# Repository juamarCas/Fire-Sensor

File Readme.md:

# Fire sensor network
This project conssists on a prototype of a Wireless Sensor Network(WSN) for fire detection.
The design is made in Ki-Cad
## Sensor node
It uses the Atmega328 (Arduino one).
connector J1 you can connect a battery to measure the energy left.

### Code
the code for each sensor is in  _Transmmiter.ino_ 
when you configure the channels you have to know that it has to be a
number in octal format like this:
```
int this_node = 01; 
```

## Base node
It uses NodeMCU with the ESP8266, 

### Code 
the code is _BaseNode2.ino_
also use octal form for channels

## Libraries
-We used the nrf24L01 library to communicate each node, you can find the library here [GitHub Pages](https://github.com/nRF24/RF24)

-To make a network we used nrf24l01 network library [GitHub Pages](https://github.com/nRF24/RF24Network)

-To meassure temperature and humidity we used the DTH22 library 
[GitHub Pages](https://github.com/adafruit/DHT-sensor-library)

-To send data to the server we used ArduinoJson [ArduinoJson] (https://arduinojson.org/)

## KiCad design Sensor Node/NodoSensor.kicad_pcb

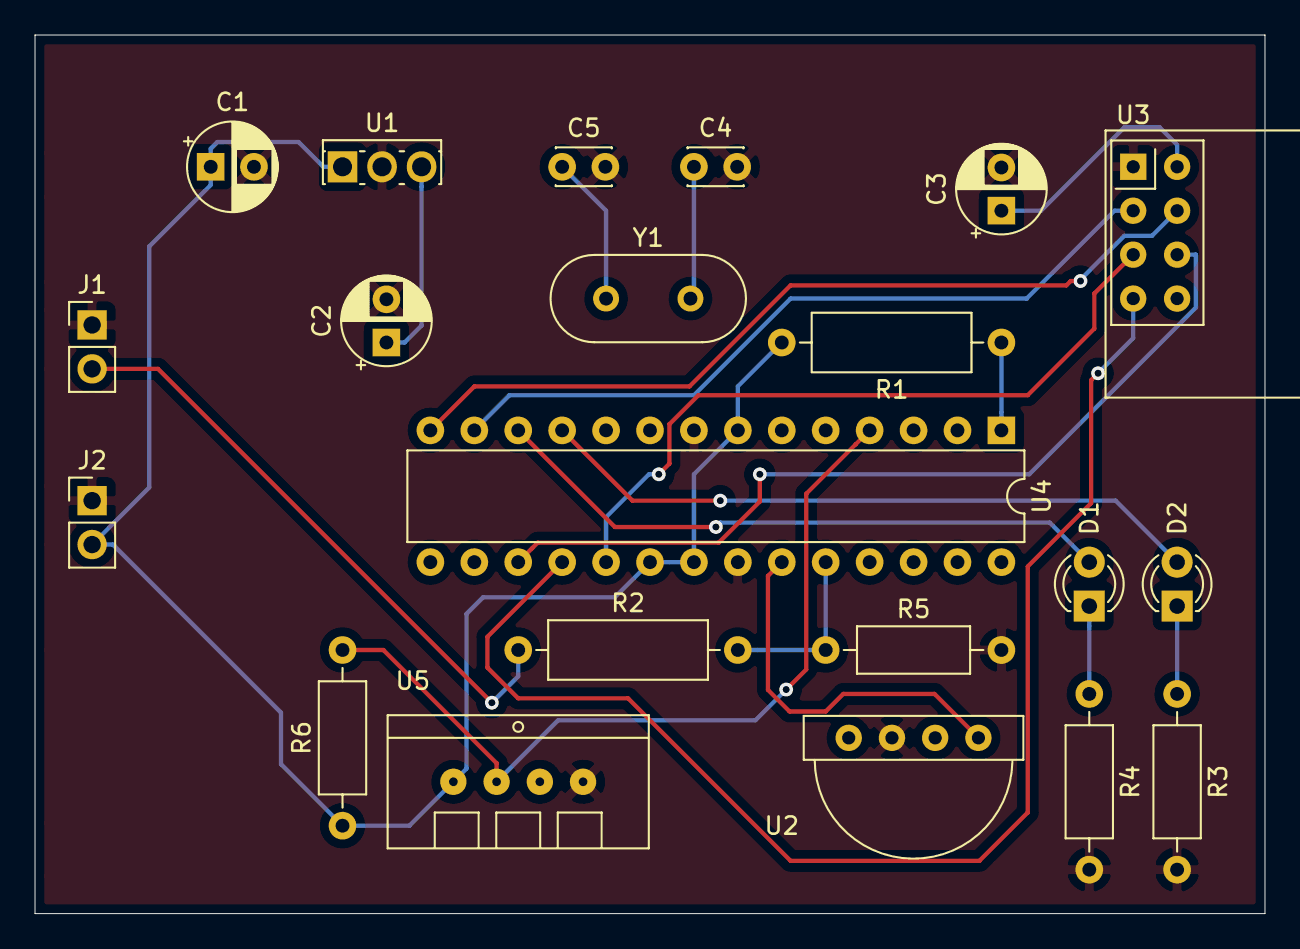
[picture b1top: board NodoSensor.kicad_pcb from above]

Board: 2 copper layers, 71.1 x 50.8 mm, 21 parts (0 on the bottom side), 19 nets.

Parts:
C1: 0.1uF; CP_Radial_D5.0mm_P2.50mm
C2: 22uF; CP_Radial_D5.0mm_P2.50mm
C3: 10uF; CP_Radial_D5.0mm_P2.50mm
C4, C5: 22pF; C_Disc_D3.0mm_W2.0mm_P2.50mm
D1, D2: LED; LED_D3.0mm
J1, J2: Conn_01x02_Female; PinHeader_1x02_P2.54mm_Vertical
R1: 10k; R_Axial_DIN0309_L9.0mm_D3.2mm_P12.70mm_Horizontal
R2: 1k; R_Axial_DIN0309_L9.0mm_D3.2mm_P12.70mm_Horizontal
R3, R4: 330; R_Axial_DIN0207_L6.3mm_D2.5mm_P10.16mm_Horizontal
R5, R6: 1k; R_Axial_DIN0207_L6.3mm_D2.5mm_P10.16mm_Horizontal
U1: TLV2217-33; SIPAK_Vertical
U2: MQ2_D
U3: NRF24L01_Breakout; nRF24L01_Breakout
U4: ATmega328P-PU; DIP-28_W7.62mm
U5: DHT22
Y1: Crystal; Crystal_HC49-U_Vertical

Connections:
+3V3: C2.1, C3.1, U1.3, U3.2
+5V: C1.1, J2.2, R1.2, R6.1, U1.1, U2.1, U4.7, U4.20, U4.21, U5.1
/ADC0: U2.4, U4.23
/ADC1: R2.2, R5.1, U4.24
/CE: U3.3, U4.13
/CSN: U3.4, U4.14
/Data: R6.2, U4.4, U5.2
/LED1: D2.2, U4.11
/LED2: D1.2, U4.12
/MISO: U3.7, U4.18
/MOSI: U3.6, U4.17
/SCK: U3.5, U4.19
GND: C1.2, C2.2, C3.2, C4.2, C5.2, J1.1, J2.1, R3.2, R4.2, R5.2, U1.2, U2.2, U3.1, U4.8, U4.22, U5.4
unnamed: D1.1, R4.1
unnamed: D2.1, R3.1
unnamed: R1.1, U4.1
VDC: J1.2, R2.1
XTAL1: C4.1, U4.9, Y1.2
XTAL2: C5.1, U4.10, Y1.1

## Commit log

2020-02-16 Started the design
